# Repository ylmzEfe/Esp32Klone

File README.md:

# Esp32Klone
A custom ESP32-based PCB designed from scratch in KiCad.  
*This is my first ESP32 and KiCad project — built to learn PCB design fundamentals.*
## Features
- ESP32-WROOM-32E module
- USB-C connectivity
- CH340G USB-to-UART bridge
- AMS1117-3.3 voltage regulator
- Automatic bootloader circuit
## Status
Completed.

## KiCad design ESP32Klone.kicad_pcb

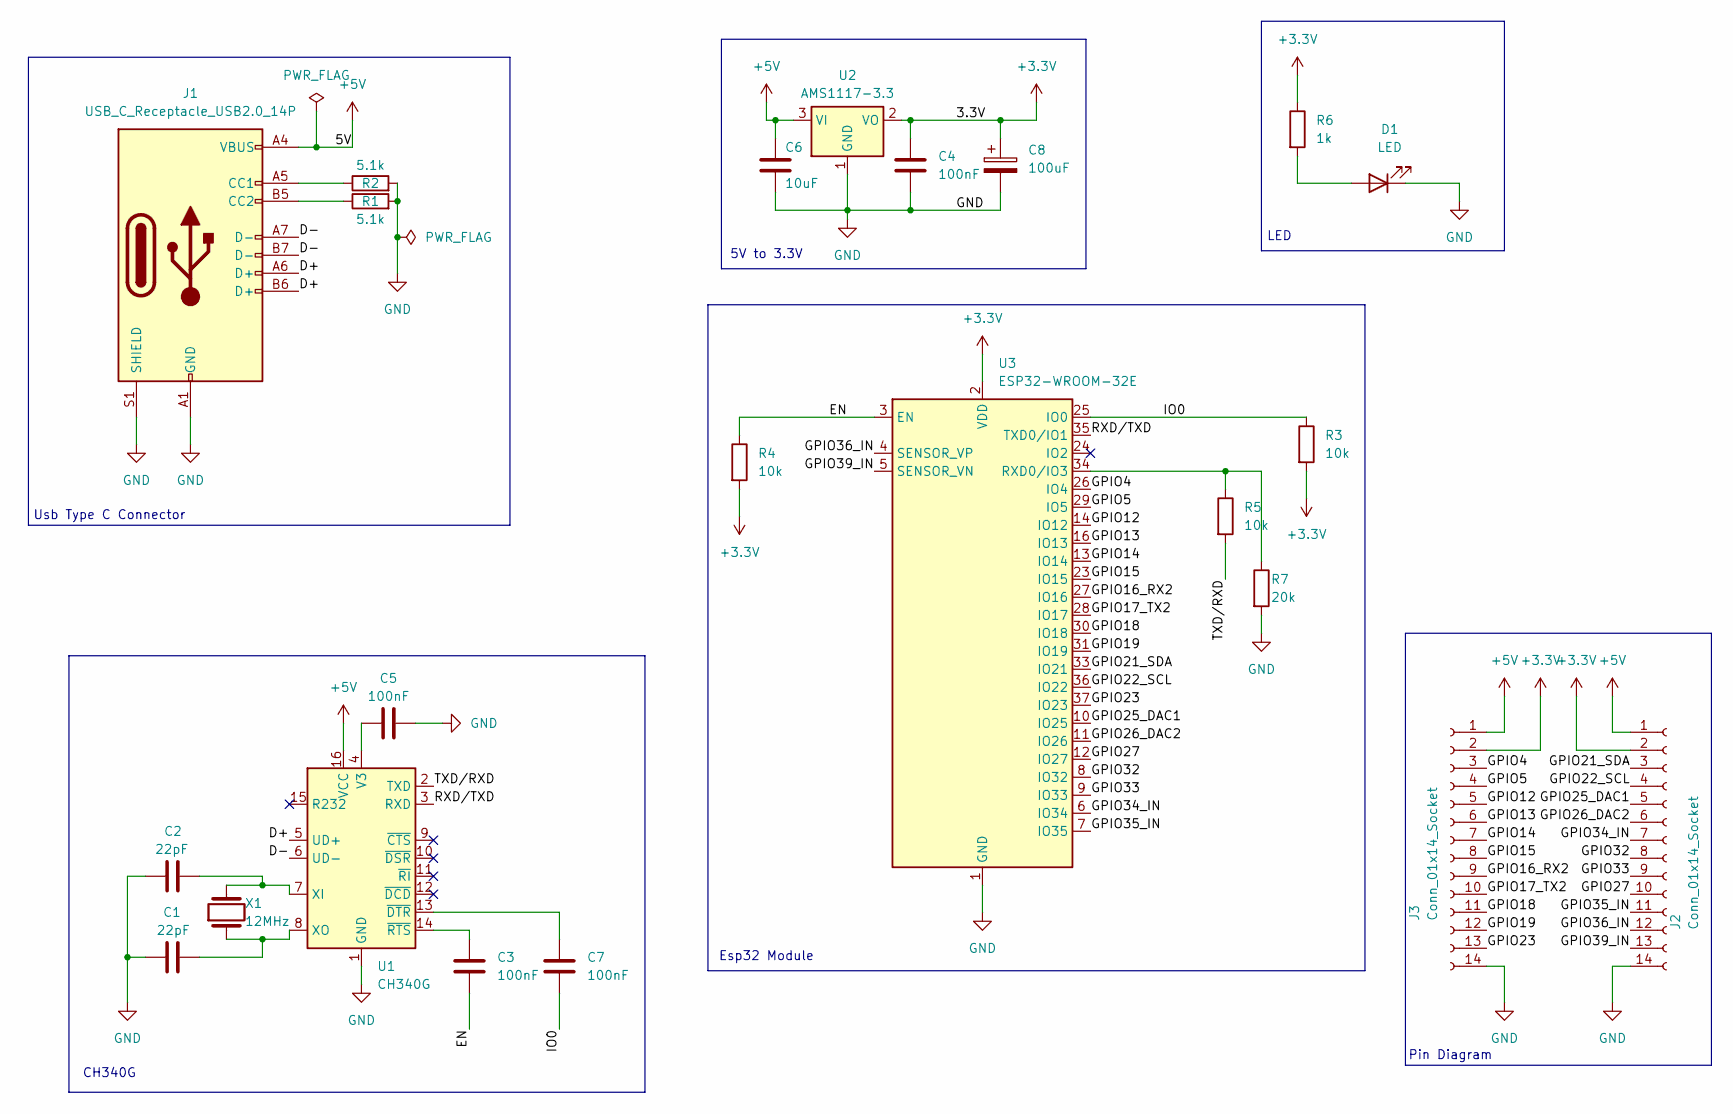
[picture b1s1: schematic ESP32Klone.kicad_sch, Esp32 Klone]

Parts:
C1, C2: 22pF; C_0603
C3, C4, C5, C7: 100nF; C_0603
C6: 10uF; C_0805
C8: 100uF; CP_Elec_6.3x5.4
D1: LED; LED_0603_1608Metric
J1: USB_C_Receptacle_USB2.0_14P; USB_C_Receptacle_HRO_TYPE-C-31-M-12
J2, J3: Conn_01x14_Socket; PinHeader_1x14_P2.54mm_Vertical
R1, R2: 5.1k; R_0603
R3, R4, R5: 10k; R_0603
R6: 1k; R_0603
R7: 20k; R_0603
U1: CH340G; SOIC-16_3.9x9.9mm_P1.27mm
U2: AMS1117-3.3; SOT-223-3_TabPin2
U3: ESP32-WROOM-32E; ESP32-WROOM-32D
X1: 12MHz; Crystal_SMD_HC49-SD

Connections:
+3.3V: C4.1, C8.1, J2.2, J3.2, R3.2, R4.2, R6.1, U2.2 (VO), U3.2 (VDD)
+5V: C6.1, J1.A4 (VBUS), J1.A9 (VBUS), J1.B4 (VBUS), J1.B9 (VBUS), J2.1, J3.1, U1.16 (VCC), U2.3 (VI)
/D+: J1.A6 (D+), J1.B6 (D+), U1.5 (UD+)
/D-: J1.A7 (D-), J1.B7 (D-), U1.6 (UD-)
/EN: C3.2, R4.1, U3.3 (EN)
/GPIO4: J3.3, U3.26 (IO4)
/GPIO5: J3.4, U3.29 (IO5)
/GPIO12: J3.5, U3.14 (IO12)
/GPIO13: J3.6, U3.16 (IO13)
/GPIO14: J3.7, U3.13 (IO14)
/GPIO15: J3.8, U3.23 (IO15)
/GPIO16_RX2: J3.9, U3.27 (IO16)
/GPIO17_TX2: J3.10, U3.28 (IO17)
/GPIO18: J3.11, U3.30 (IO18)
/GPIO19: J3.12, U3.31 (IO19)
/GPIO21_SDA: J2.3, U3.33 (IO21)
/GPIO22_SCL: J2.4, U3.36 (IO22)
/GPIO23: J3.13, U3.37 (IO23)
/GPIO25_DAC1: J2.5, U3.10 (IO25)
/GPIO26_DAC2: J2.6, U3.11 (IO26)
/GPIO27: J2.10, U3.12 (IO27)
/GPIO32: J2.8, U3.8 (IO32)
/GPIO33: J2.9, U3.9 (IO33)
/GPIO34_IN: J2.7, U3.6 (IO34)
/GPIO35_IN: J2.11, U3.7 (IO35)
/GPIO36_IN: J2.12, U3.4 (SENSOR_VP)
/GPIO39_IN: J2.13, U3.5 (SENSOR_VN)
/IO0: C7.2, R3.1, U3.25 (IO0)
/RXD/TXD: U1.3 (RXD), U3.35 (TXD0/IO1)
/TXD/RXD: R5.2, U1.2 (TXD)
GND: C1.1, C2.1, C4.2, C5.2, C6.2, C8.2, D1.1 (K), J1.A1 (GND), J1.A12 (GND), J1.B1 (GND), J1.B12 (GND), J1.S1 (SHIELD), J2.14, J3.14, R1.2, R2.2, R7.2, U1.1 (GND), U2.1 (GND), U3.1 (GND), U3.15 (GND), U3.38 (GND), U3.39 (GND)
unnamed: D1.2 (A), R6.2
unnamed: J1.A5 (CC1), R2.1
unnamed: J1.B5 (CC2), R1.1
unnamed: C5.1, U1.4 (V3)
unnamed: C2.2, U1.7 (XI), X1.2
unnamed: C1.2, U1.8 (XO), X1.1
unnamed: C7.1, U1.13 (~DTR)
unnamed: C3.1, U1.14 (~RTS)
unnamed: R5.1, R7.1, U3.34 (RXD0/IO3)

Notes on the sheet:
CH340G
Usb Type C Connector
Pin Diagram
5V to 3.3V
Esp32 Module
LED

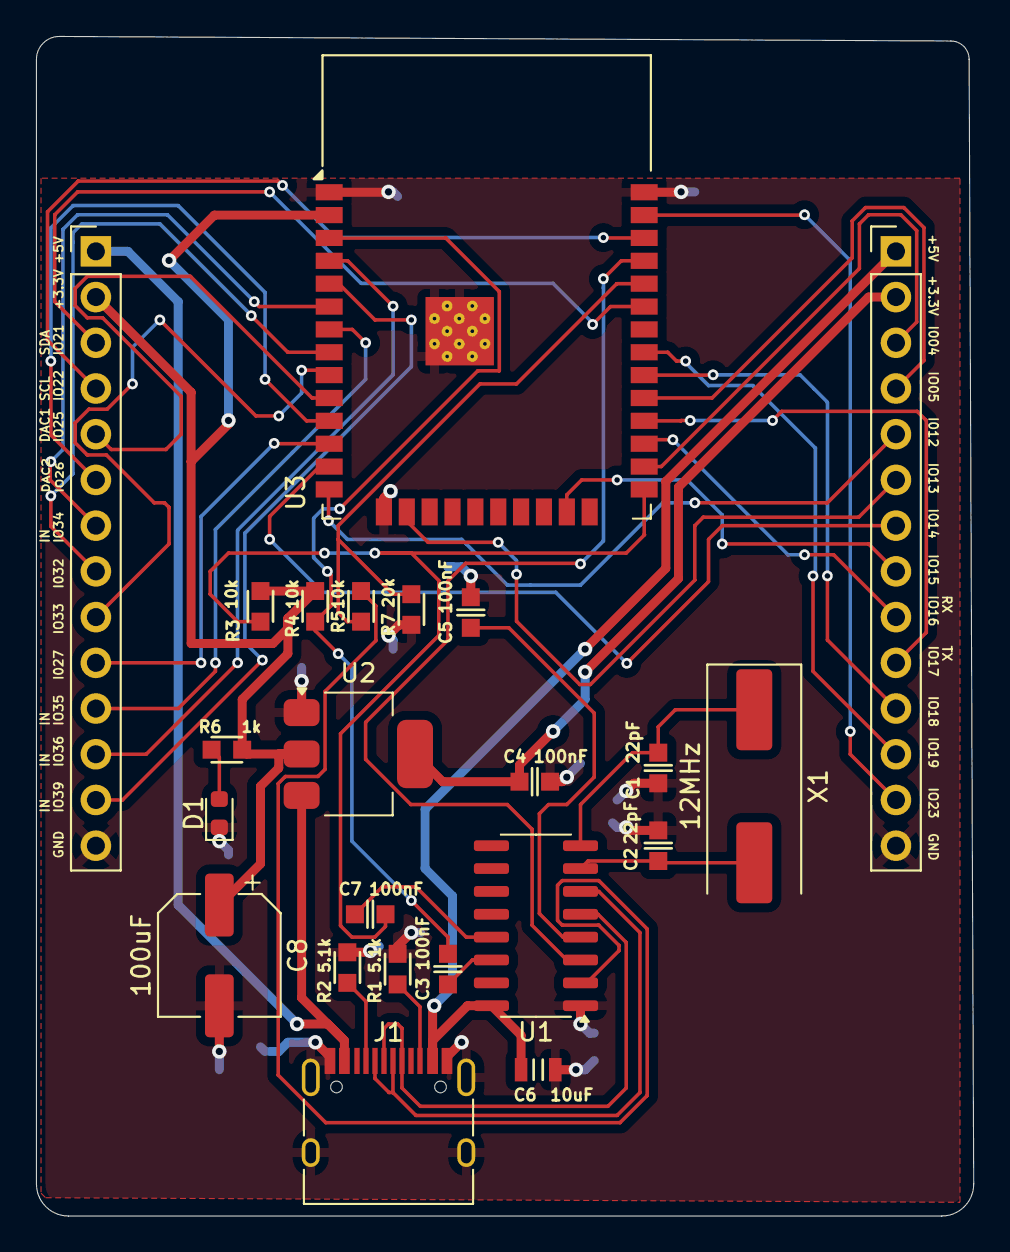
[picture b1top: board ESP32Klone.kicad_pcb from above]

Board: 2 copper layers, 52.1 x 65.5 mm, 23 parts (0 on the bottom side), 40 nets.

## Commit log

2026-04-10 Create LICENSE
2026-04-10 Esp32 ilk
2026-04-11 Update LICENSE
2026-04-13 fix: correct UART Rx level shifter wiring (R5/R7)
2026-04-28 Added F.Cu copperfill
2026-05-01 fix: silkscreen GPIO39 label corrected
